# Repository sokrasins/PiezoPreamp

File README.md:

# Piezo Preamp

A preamp/impedance-matching circuit for piezoelectric disks.

Layout forked from <https://github.com/mo-seph/PiezoPreamp>.

Design notes from <https://www.zachpoff.com/resources/alex-rice-piezo-preamplifier/>.

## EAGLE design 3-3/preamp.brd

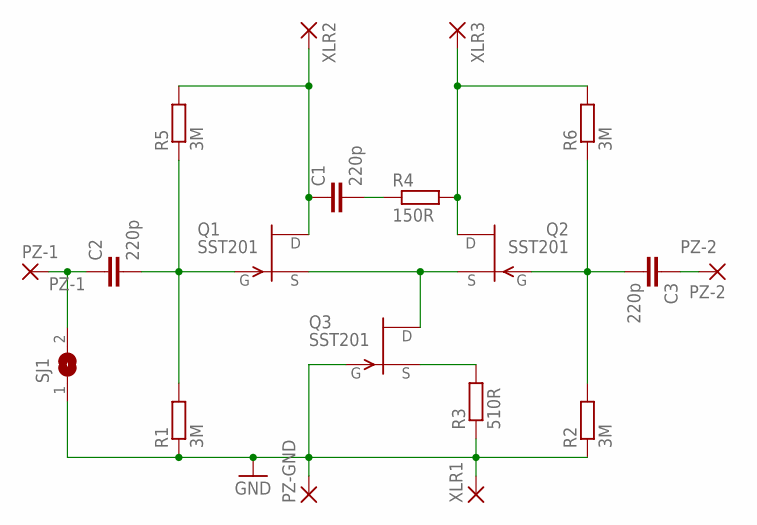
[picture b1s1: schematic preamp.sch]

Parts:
C1, C2, C3: 220p; C1206
PZ-1, PZ-2: 3,17/1,3
PZ-GND: 3,17/1,3
Q1, Q2, Q3: SST201; SOT23
R1, R2, R5, R6: 3M; R1206
R3: 510R; R1206
R4: 150R; R1206
SJ1: SJ
XLR1, XLR2, XLR3: 3,17/1,3

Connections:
GND: PZ-GND.1, Q3.3 (G), R1.1, R2.1, R3.1, SJ1.1, XLR1.1
unnamed: Q1.2 (S), Q2.2 (S), Q3.1 (D)
unnamed: C2.2, Q1.3 (G), R1.2, R5.1
unnamed: C1.2, R4.1
unnamed: C3.2, Q2.3 (G), R2.2, R6.1
unnamed: Q3.2 (S), R3.2
PZ-1: C2.1, PZ-1.1, SJ1.2
PZ-2: C3.1, PZ-2.1
XLR3: Q2.1 (D), R4.2, R6.2, XLR3.1
XLR-2: C1.1, Q1.1 (D), R5.2, XLR2.1

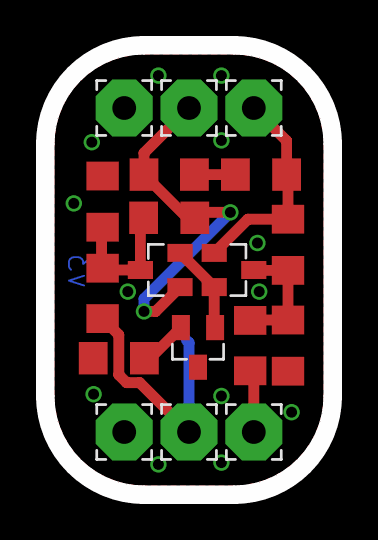
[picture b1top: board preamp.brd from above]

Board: 2 copper layers, 16.0 x 25.0 mm, 19 parts (1 on the bottom side), 10 nets.

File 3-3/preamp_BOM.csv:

Ref Des,Value,Qty,MFR,MFR #,Mouser #
"R1, R2, R5, R6",3M,4,Vishay Semiconductors,CRCW12063M00JNEA,71-CRCW12063M00JNEA
R3,510R,1,Yageo,AC1206FR-07510RL,603-AC1206FR-07510RL
R4,150R,1,Yageo,RC1206FR-07150RL,603-RC1206FR-07150RL
"C1, C2, C3",220pF,3,Wurth Electronics,885012008045,710-885012008045
"Q1, Q2, Q3",SST201,3,Vishay Semiconductors,SST201-T1-E3,781-SST201-T1-E3

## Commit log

2018-11-22 Add first board run
2018-11-22 add gitignore
2018-11-22 Change gain resistor to match IRL, add TODO notes
2018-11-22 Folder structure
2018-11-25 Added cap pads, pot holes
2018-11-25 Remove part names
2018-11-25 Move silk location
2018-12-05 Added rev3, only silk changes
2018-12-05 Added readme
2018-12-06 Base 3-3 after 1-1 after building 2-2
2018-12-06 Add BOM
2018-12-06 Added label for solder jumper
2018-12-06 oops, put text on silk layer
